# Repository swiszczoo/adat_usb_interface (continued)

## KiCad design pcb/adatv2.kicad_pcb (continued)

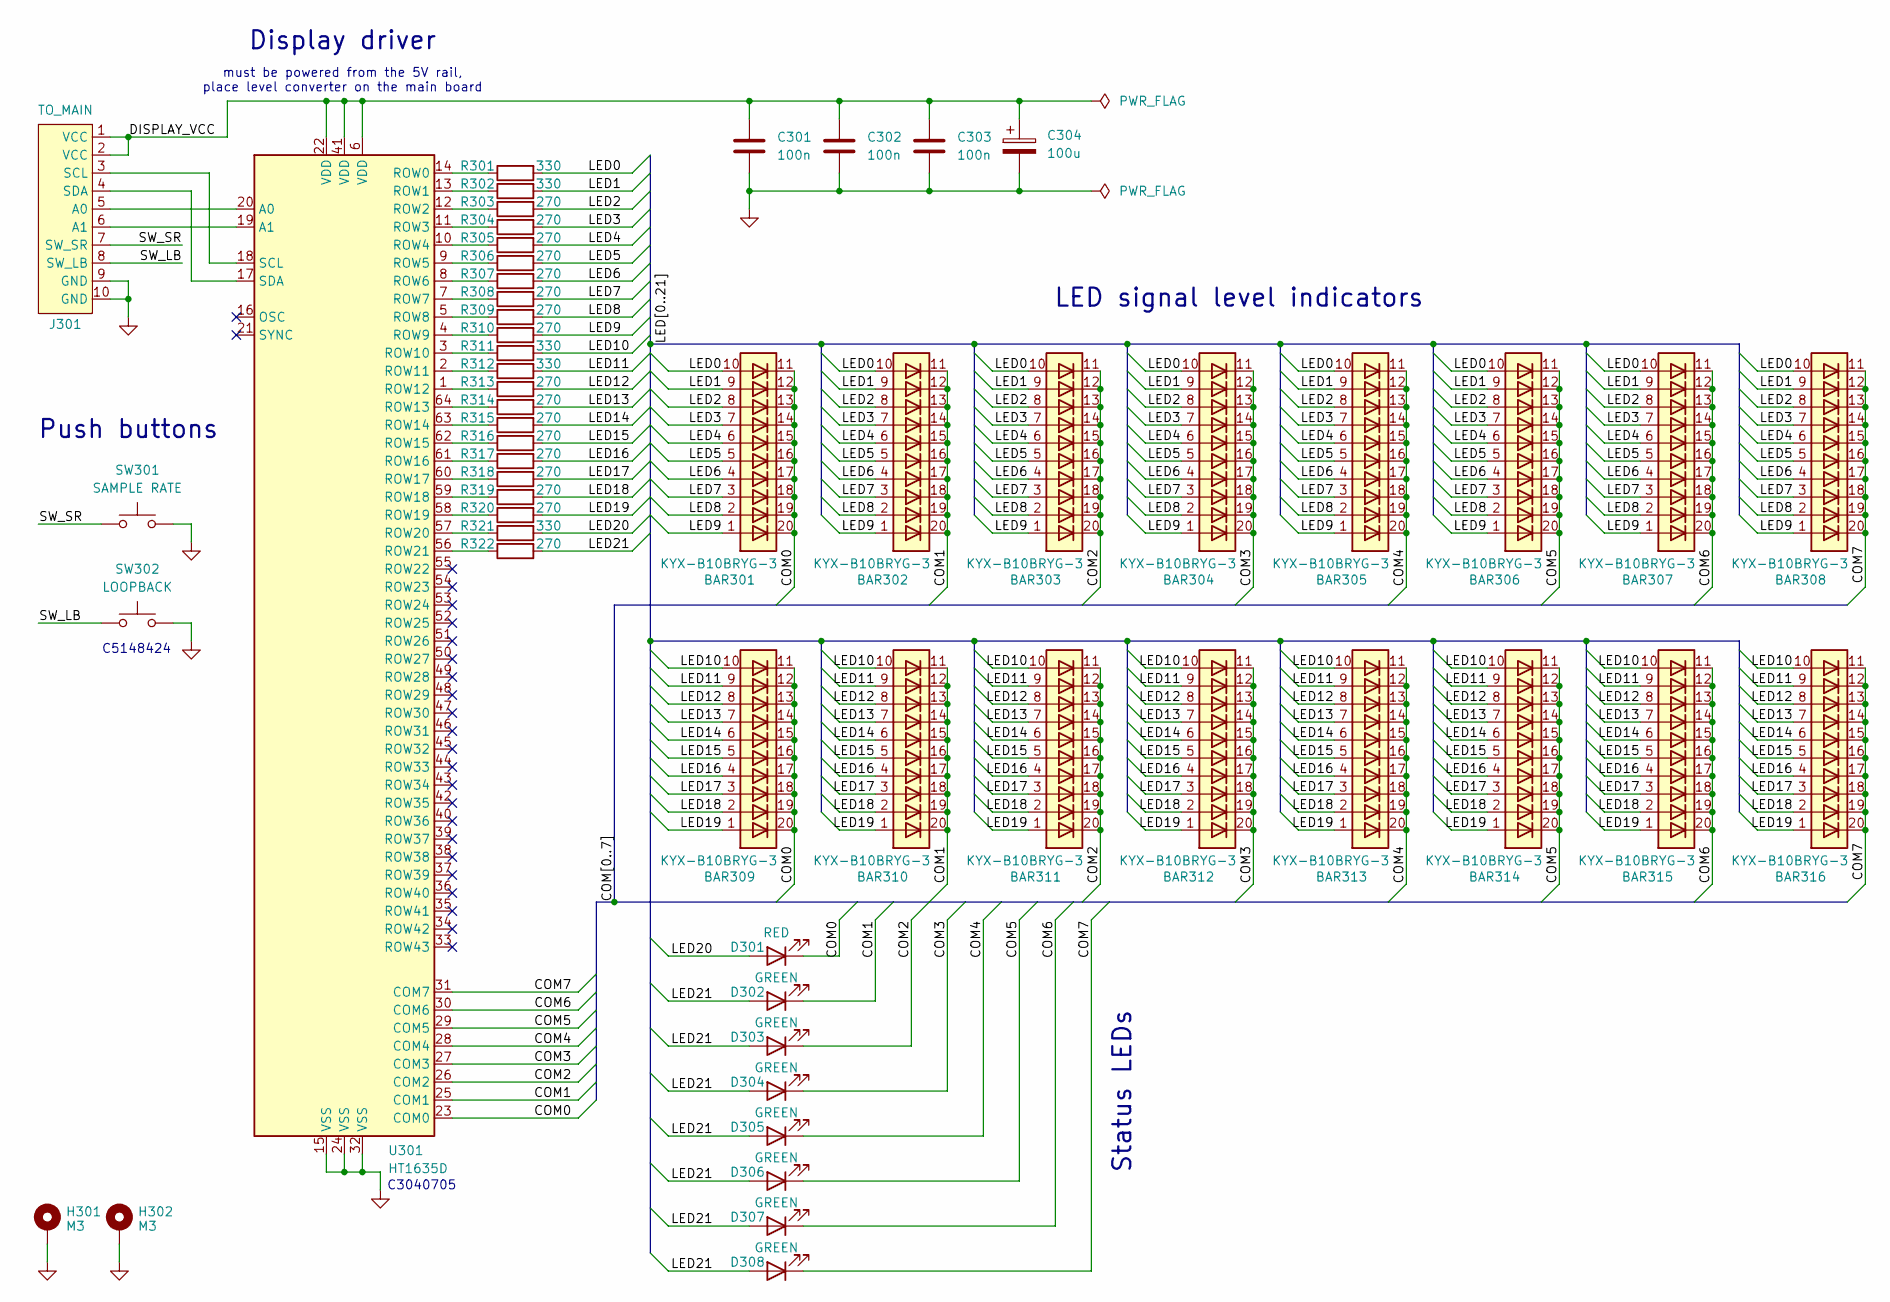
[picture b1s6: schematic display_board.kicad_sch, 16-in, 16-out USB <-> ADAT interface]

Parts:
BAR301, BAR302, BAR303, BAR304, BAR305, BAR306, BAR307, BAR308, BAR309, BAR310, BAR311, BAR312, BAR313, BAR314, BAR315, BAR316: KYX-B10BRYG-3; LED_10bar
C301, C302, C303: 100n; C_0805_2012Metric_Pad1.18x1.45mm_HandSolder
C304: 100u; C_Elec_6.3x5.4
D301: RED; LED_THT_W7.0mm_H2.00mm
D302, D303, D304, D305, D306, D307, D308: GREEN; LED_THT_W7.0mm_H2.00mm
H301, H302: M3; MountingHole_3.2mm_M3_Pad
J301: TO_MAIN; IDC-Header_2x05_P2.54mm_Vertical
R301, R302, R311, R312, R321: 330; R_0805_2012Metric_Pad1.20x1.40mm_HandSolder
R303, R304, R305, R306, R307, R308, R309, R310, R313, R314, R315, R316, R317, R318, R319, R320, R322: 270; R_0805_2012Metric_Pad1.20x1.40mm_HandSolder
SW301: SAMPLE RATE; SW_Push_1P1T_NO_CK_PTS125Sx43SMTR
SW302: LOOPBACK; SW_Push_1P1T_NO_CK_PTS125Sx43SMTR
U301: HT1635D; LQFP-64_7x7mm_P0.4mm

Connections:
/Display board/COM0: BAR301.11 (K), BAR301.12 (K), BAR301.13 (K), BAR301.14 (K), BAR301.15 (K), BAR301.16 (K), BAR301.17 (K), BAR301.18 (K), BAR301.19 (K), BAR301.20 (K), BAR309.11 (K), BAR309.12 (K), BAR309.13 (K), BAR309.14 (K), BAR309.15 (K), BAR309.16 (K), BAR309.17 (K), BAR309.18 (K), BAR309.19 (K), BAR309.20 (K), D301.1 (K), U301.23 (COM0)
/Display board/COM1: BAR302.11 (K), BAR302.12 (K), BAR302.13 (K), BAR302.14 (K), BAR302.15 (K), BAR302.16 (K), BAR302.17 (K), BAR302.18 (K), BAR302.19 (K), BAR302.20 (K), BAR310.11 (K), BAR310.12 (K), BAR310.13 (K), BAR310.14 (K), BAR310.15 (K), BAR310.16 (K), BAR310.17 (K), BAR310.18 (K), BAR310.19 (K), BAR310.20 (K), D302.1 (K), U301.25 (COM1)
/Display board/COM2: BAR303.11 (K), BAR303.12 (K), BAR303.13 (K), BAR303.14 (K), BAR303.15 (K), BAR303.16 (K), BAR303.17 (K), BAR303.18 (K), BAR303.19 (K), BAR303.20 (K), BAR311.11 (K), BAR311.12 (K), BAR311.13 (K), BAR311.14 (K), BAR311.15 (K), BAR311.16 (K), BAR311.17 (K), BAR311.18 (K), BAR311.19 (K), BAR311.20 (K), D303.1 (K), U301.26 (COM2)
/Display board/COM3: BAR304.11 (K), BAR304.12 (K), BAR304.13 (K), BAR304.14 (K), BAR304.15 (K), BAR304.16 (K), BAR304.17 (K), BAR304.18 (K), BAR304.19 (K), BAR304.20 (K), BAR312.11 (K), BAR312.12 (K), BAR312.13 (K), BAR312.14 (K), BAR312.15 (K), BAR312.16 (K), BAR312.17 (K), BAR312.18 (K), BAR312.19 (K), BAR312.20 (K), D304.1 (K), U301.27 (COM3)
/Display board/COM4: BAR305.11 (K), BAR305.12 (K), BAR305.13 (K), BAR305.14 (K), BAR305.15 (K), BAR305.16 (K), BAR305.17 (K), BAR305.18 (K), BAR305.19 (K), BAR305.20 (K), BAR313.11 (K), BAR313.12 (K), BAR313.13 (K), BAR313.14 (K), BAR313.15 (K), BAR313.16 (K), BAR313.17 (K), BAR313.18 (K), BAR313.19 (K), BAR313.20 (K), D305.1 (K), U301.28 (COM4)
/Display board/COM5: BAR306.11 (K), BAR306.12 (K), BAR306.13 (K), BAR306.14 (K), BAR306.15 (K), BAR306.16 (K), BAR306.17 (K), BAR306.18 (K), BAR306.19 (K), BAR306.20 (K), BAR314.11 (K), BAR314.12 (K), BAR314.13 (K), BAR314.14 (K), BAR314.15 (K), BAR314.16 (K), BAR314.17 (K), BAR314.18 (K), BAR314.19 (K), BAR314.20 (K), D306.1 (K), U301.29 (COM5)
/Display board/COM6: BAR307.11 (K), BAR307.12 (K), BAR307.13 (K), BAR307.14 (K), BAR307.15 (K), BAR307.16 (K), BAR307.17 (K), BAR307.18 (K), BAR307.19 (K), BAR307.20 (K), BAR315.11 (K), BAR315.12 (K), BAR315.13 (K), BAR315.14 (K), BAR315.15 (K), BAR315.16 (K), BAR315.17 (K), BAR315.18 (K), BAR315.19 (K), BAR315.20 (K), D307.1 (K), U301.30 (COM6)
/Display board/COM7: BAR308.11 (K), BAR308.12 (K), BAR308.13 (K), BAR308.14 (K), BAR308.15 (K), BAR308.16 (K), BAR308.17 (K), BAR308.18 (K), BAR308.19 (K), BAR308.20 (K), BAR316.11 (K), BAR316.12 (K), BAR316.13 (K), BAR316.14 (K), BAR316.15 (K), BAR316.16 (K), BAR316.17 (K), BAR316.18 (K), BAR316.19 (K), BAR316.20 (K), D308.1 (K), U301.31 (COM7)
/Display board/DISPLAY_VCC: C301.1, C302.1, C303.1, C304.1, J301.1 (VCC), J301.2 (VCC), U301.6 (VDD), U301.22 (VDD), U301.41 (VDD)
/Display board/LED0: BAR301.10 (A), BAR302.10 (A), BAR303.10 (A), BAR304.10 (A), BAR305.10 (A), BAR306.10 (A), BAR307.10 (A), BAR308.10 (A), R301.2
/Display board/LED1: BAR301.9 (A), BAR302.9 (A), BAR303.9 (A), BAR304.9 (A), BAR305.9 (A), BAR306.9 (A), BAR307.9 (A), BAR308.9 (A), R302.2
/Display board/LED2: BAR301.8 (A), BAR302.8 (A), BAR303.8 (A), BAR304.8 (A), BAR305.8 (A), BAR306.8 (A), BAR307.8 (A), BAR308.8 (A), R303.2
/Display board/LED3: BAR301.7 (A), BAR302.7 (A), BAR303.7 (A), BAR304.7 (A), BAR305.7 (A), BAR306.7 (A), BAR307.7 (A), BAR308.7 (A), R304.2
/Display board/LED4: BAR301.6 (A), BAR302.6 (A), BAR303.6 (A), BAR304.6 (A), BAR305.6 (A), BAR306.6 (A), BAR307.6 (A), BAR308.6 (A), R305.2
/Display board/LED5: BAR301.5 (A), BAR302.5 (A), BAR303.5 (A), BAR304.5 (A), BAR305.5 (A), BAR306.5 (A), BAR307.5 (A), BAR308.5 (A), R306.2
/Display board/LED6: BAR301.4 (A), BAR302.4 (A), BAR303.4 (A), BAR304.4 (A), BAR305.4 (A), BAR306.4 (A), BAR307.4 (A), BAR308.4 (A), R307.2
/Display board/LED7: BAR301.3 (A), BAR302.3 (A), BAR303.3 (A), BAR304.3 (A), BAR305.3 (A), BAR306.3 (A), BAR307.3 (A), BAR308.3 (A), R308.2
/Display board/LED8: BAR301.2 (A), BAR302.2 (A), BAR303.2 (A), BAR304.2 (A), BAR305.2 (A), BAR306.2 (A), BAR307.2 (A), BAR308.2 (A), R309.2
/Display board/LED9: BAR301.1 (A), BAR302.1 (A), BAR303.1 (A), BAR304.1 (A), BAR305.1 (A), BAR306.1 (A), BAR307.1 (A), BAR308.1 (A), R310.2
/Display board/LED10: BAR309.10 (A), BAR310.10 (A), BAR311.10 (A), BAR312.10 (A), BAR313.10 (A), BAR314.10 (A), BAR315.10 (A), BAR316.10 (A), R311.2
/Display board/LED11: BAR309.9 (A), BAR310.9 (A), BAR311.9 (A), BAR312.9 (A), BAR313.9 (A), BAR314.9 (A), BAR315.9 (A), BAR316.9 (A), R312.2
/Display board/LED12: BAR309.8 (A), BAR310.8 (A), BAR311.8 (A), BAR312.8 (A), BAR313.8 (A), BAR314.8 (A), BAR315.8 (A), BAR316.8 (A), R313.2
/Display board/LED13: BAR309.7 (A), BAR310.7 (A), BAR311.7 (A), BAR312.7 (A), BAR313.7 (A), BAR314.7 (A), BAR315.7 (A), BAR316.7 (A), R314.2
/Display board/LED14: BAR309.6 (A), BAR310.6 (A), BAR311.6 (A), BAR312.6 (A), BAR313.6 (A), BAR314.6 (A), BAR315.6 (A), BAR316.6 (A), R315.2
/Display board/LED15: BAR309.5 (A), BAR310.5 (A), BAR311.5 (A), BAR312.5 (A), BAR313.5 (A), BAR314.5 (A), BAR315.5 (A), BAR316.5 (A), R316.2
/Display board/LED16: BAR309.4 (A), BAR310.4 (A), BAR311.4 (A), BAR312.4 (A), BAR313.4 (A), BAR314.4 (A), BAR315.4 (A), BAR316.4 (A), R317.2
/Display board/LED17: BAR309.3 (A), BAR310.3 (A), BAR311.3 (A), BAR312.3 (A), BAR313.3 (A), BAR314.3 (A), BAR315.3 (A), BAR316.3 (A), R318.2
/Display board/LED18: BAR309.2 (A), BAR310.2 (A), BAR311.2 (A), BAR312.2 (A), BAR313.2 (A), BAR314.2 (A), BAR315.2 (A), BAR316.2 (A), R319.2
/Display board/LED19: BAR309.1 (A), BAR310.1 (A), BAR311.1 (A), BAR312.1 (A), BAR313.1 (A), BAR314.1 (A), BAR315.1 (A), BAR316.1 (A), R320.2
/Display board/LED20: D301.2 (A), R321.2
/Display board/LED21: D302.2 (A), D303.2 (A), D304.2 (A), D305.2 (A), D306.2 (A), D307.2 (A), D308.2 (A), R322.2
/Display board/SW_LB: J301.8 (SW_LB), SW302.1
/Display board/SW_SR: J301.7 (SW_SR), SW301.1
DISPLAY_GND: C301.2, C302.2, C303.2, C304.2, H301.1, H302.1, J301.9 (GND), J301.10 (GND), SW301.2, SW302.2, U301.15 (VSS), U301.24 (VSS), U301.32 (VSS)
unnamed: J301.5 (A0), U301.20 (A0)
unnamed: J301.6 (A1), U301.19 (A1)
unnamed: J301.3 (SCL), U301.18 (SCL)
unnamed: J301.4 (SDA), U301.17 (SDA)
unnamed: R301.1, U301.14 (ROW0)
unnamed: R302.1, U301.13 (ROW1)
unnamed: R303.1, U301.12 (ROW2)
unnamed: R304.1, U301.11 (ROW3)
unnamed: R305.1, U301.10 (ROW4)
unnamed: R306.1, U301.9 (ROW5)
unnamed: R307.1, U301.8 (ROW6)
unnamed: R308.1, U301.7 (ROW7)
unnamed: R309.1, U301.5 (ROW8)
unnamed: R310.1, U301.4 (ROW9)
unnamed: R311.1, U301.3 (ROW10)
unnamed: R312.1, U301.2 (ROW11)
unnamed: R313.1, U301.1 (ROW12)
unnamed: R314.1, U301.64 (ROW13)
unnamed: R315.1, U301.63 (ROW14)
unnamed: R316.1, U301.62 (ROW15)
unnamed: R317.1, U301.61 (ROW16)
unnamed: R318.1, U301.60 (ROW17)
unnamed: R319.1, U301.59 (ROW18)
unnamed: R320.1, U301.58 (ROW19)
unnamed: R321.1, U301.57 (ROW20)
unnamed: R322.1, U301.56 (ROW21)

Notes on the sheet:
C3040705
Status LEDs
Display driver
LED signal level indicators
C5148424
must be powered from the 5V rail, place level converter on the main board
Push buttons

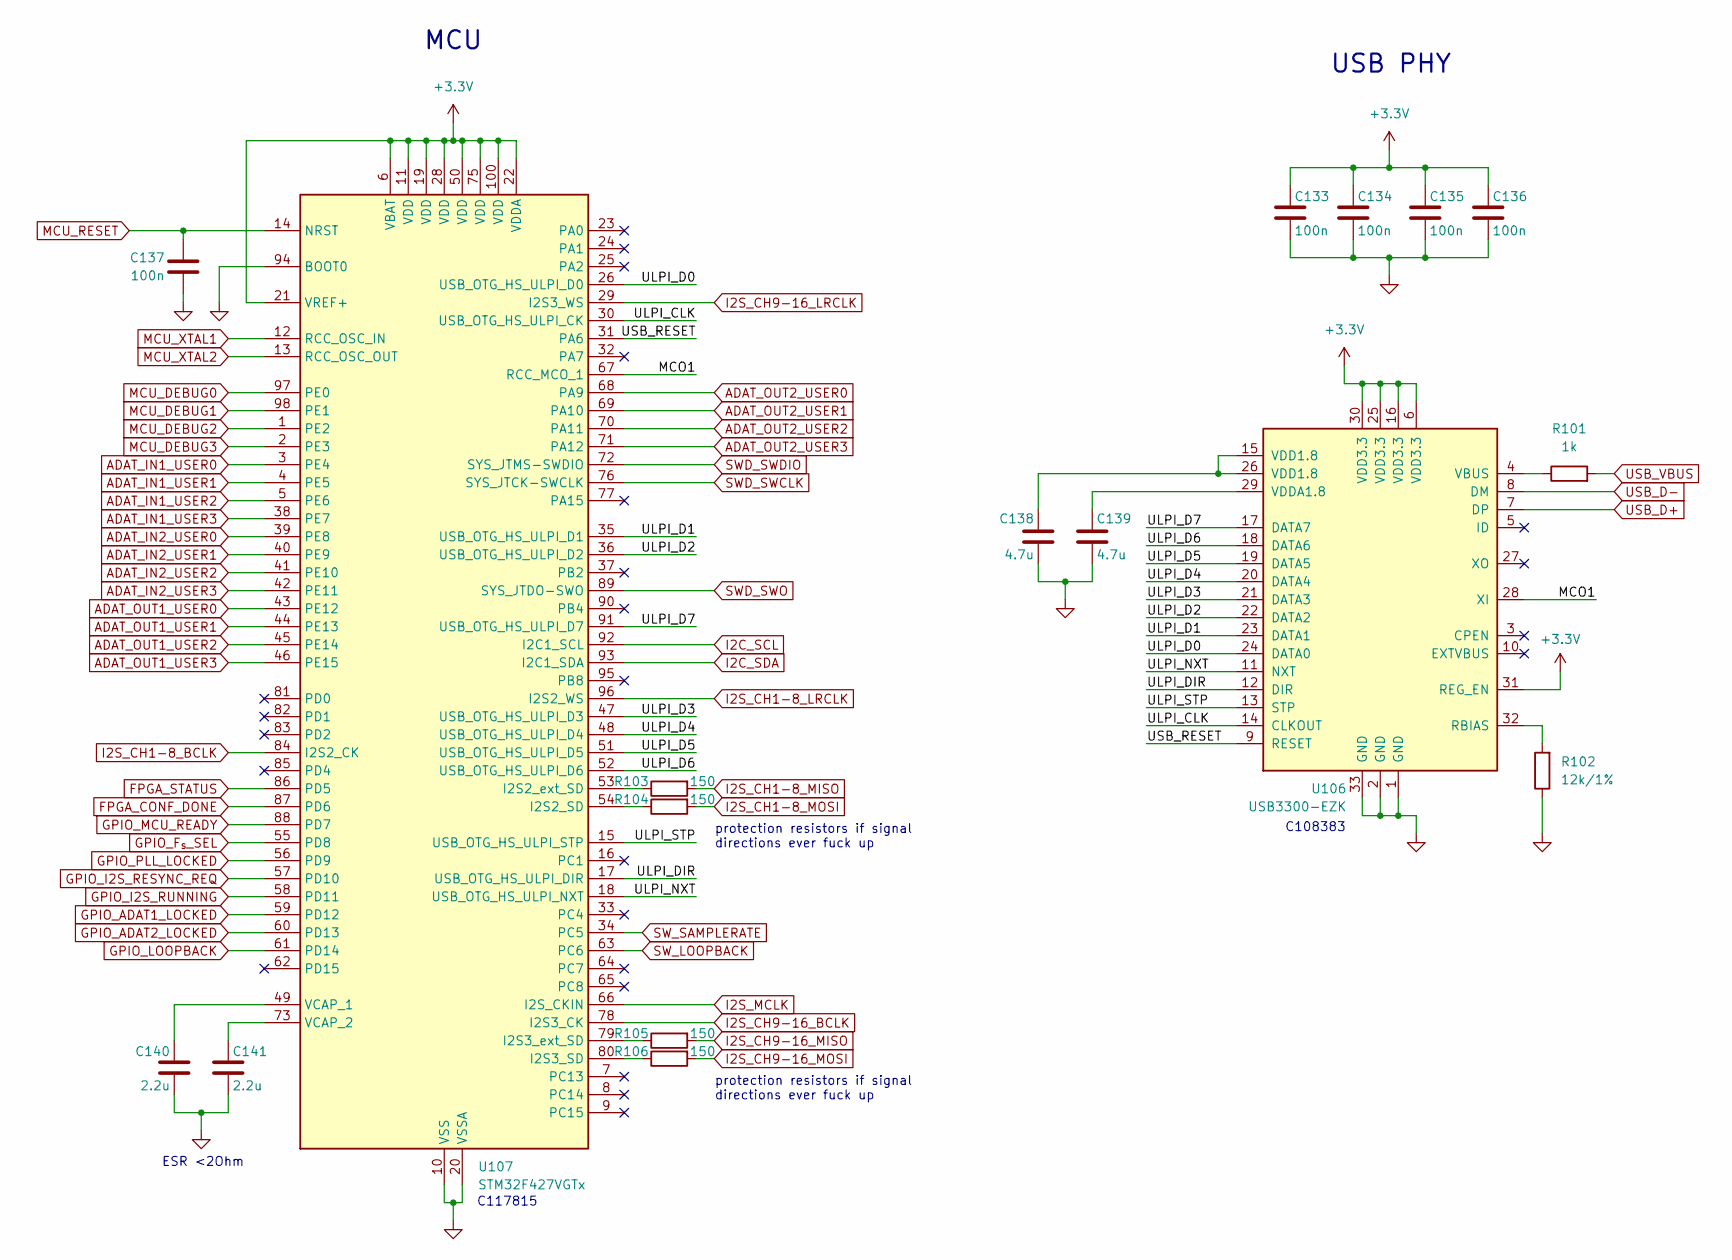
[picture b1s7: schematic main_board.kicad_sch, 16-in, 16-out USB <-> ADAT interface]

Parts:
C133, C134, C135, C136, C137: 100n; C_0805_2012Metric_Pad1.18x1.45mm_HandSolder
C138, C139: 4.7u; C_0805_2012Metric_Pad1.18x1.45mm_HandSolder
C140, C141: 2.2u; C_0805_2012Metric_Pad1.18x1.45mm_HandSolder
R101: 1k; R_0805_2012Metric_Pad1.20x1.40mm_HandSolder
R102: 12k/1%; R_0805_2012Metric_Pad1.20x1.40mm_HandSolder
R103, R104, R105, R106: 150; R_0805_2012Metric_Pad1.20x1.40mm_HandSolder
U106: USB3300-EZK; QFN-32-1EP_5x5mm_P0.5mm_EP3.45x3.45mm
U107: STM32F427VGTx; LQFP-100_14x14mm_P0.5mm

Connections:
+3.3V: C133.1, C134.1, C135.1, C136.1, U106.6 (VDD3.3), U106.16 (VDD3.3), U106.25 (VDD3.3), U106.30 (VDD3.3), U106.31 (REG_EN), U107.6 (VBAT), U107.11 (VDD), U107.19 (VDD), U107.21 (VREF+), U107.22 (VDDA), U107.28 (VDD), U107.50 (VDD), U107.75 (VDD), U107.100 (VDD); also elsewhere on the board
/MCU and USB/MCO1: U106.28 (XI), U107.67 (RCC_MCO_1)
/MCU and USB/ULPI_CLK: U106.14 (CLKOUT), U107.30 (USB_OTG_HS_ULPI_CK)
/MCU and USB/ULPI_D0: U106.24 (DATA0), U107.26 (USB_OTG_HS_ULPI_D0)
/MCU and USB/ULPI_D1: U106.23 (DATA1), U107.35 (USB_OTG_HS_ULPI_D1)
/MCU and USB/ULPI_D2: U106.22 (DATA2), U107.36 (USB_OTG_HS_ULPI_D2)
/MCU and USB/ULPI_D3: U106.21 (DATA3), U107.47 (USB_OTG_HS_ULPI_D3)
/MCU and USB/ULPI_D4: U106.20 (DATA4), U107.48 (USB_OTG_HS_ULPI_D4)
/MCU and USB/ULPI_D5: U106.19 (DATA5), U107.51 (USB_OTG_HS_ULPI_D5)
/MCU and USB/ULPI_D6: U106.18 (DATA6), U107.52 (USB_OTG_HS_ULPI_D6)
/MCU and USB/ULPI_D7: U106.17 (DATA7), U107.91 (USB_OTG_HS_ULPI_D7)
/MCU and USB/ULPI_DIR: U106.12 (DIR), U107.17 (USB_OTG_HS_ULPI_DIR)
/MCU and USB/ULPI_NXT: U106.11 (NXT), U107.18 (USB_OTG_HS_ULPI_NXT)
/MCU and USB/ULPI_STP: U106.13 (STP), U107.15 (USB_OTG_HS_ULPI_STP)
/MCU and USB/USB_RESET: U106.9 (RESET), U107.31 (PA6)
ADAT_IN1_USER0: U107.3 (PE4); also elsewhere on the board
ADAT_IN1_USER1: U107.4 (PE5); also elsewhere on the board
ADAT_IN1_USER2: U107.5 (PE6); also elsewhere on the board
ADAT_IN1_USER3: U107.38 (PE7); also elsewhere on the board
ADAT_IN2_USER0: U107.39 (PE8); also elsewhere on the board
ADAT_IN2_USER1: U107.40 (PE9); also elsewhere on the board
ADAT_IN2_USER2: U107.41 (PE10); also elsewhere on the board
ADAT_IN2_USER3: U107.42 (PE11); also elsewhere on the board
ADAT_OUT1_USER0: U107.43 (PE12); also elsewhere on the board
ADAT_OUT1_USER1: U107.44 (PE13); also elsewhere on the board
ADAT_OUT1_USER2: U107.45 (PE14); also elsewhere on the board
ADAT_OUT1_USER3: U107.46 (PE15); also elsewhere on the board
ADAT_OUT2_USER0: U107.68 (PA9); also elsewhere on the board
ADAT_OUT2_USER1: U107.69 (PA10); also elsewhere on the board
ADAT_OUT2_USER2: U107.70 (PA11); also elsewhere on the board
ADAT_OUT2_USER3: U107.71 (PA12); also elsewhere on the board
FPGA_CONF_DONE: U107.87 (PD6); also elsewhere on the board
FPGA_STATUS: U107.86 (PD5); also elsewhere on the board
GND: C133.2, C134.2, C135.2, C136.2, C137.2, C138.2, C139.2, C140.2, C141.2, R102.1, U106.1 (GND), U106.2 (GND), U106.33 (GND), U107.10 (VSS), U107.20 (VSSA), U107.27 (VSS), U107.74 (VSS), U107.94 (BOOT0), U107.99 (VSS); also elsewhere on the board
GPIO_ADAT1_LOCKED: U107.59 (PD12); also elsewhere on the board
GPIO_ADAT2_LOCKED: U107.60 (PD13); also elsewhere on the board
GPIO_F_{s}_SEL: U107.55 (PD8); also elsewhere on the board
GPIO_I2S_RESYNC_REQ: U107.57 (PD10); also elsewhere on the board
GPIO_I2S_RUNNING: U107.58 (PD11); also elsewhere on the board
GPIO_LOOPBACK: U107.61 (PD14); also elsewhere on the board
GPIO_MCU_READY: U107.88 (PD7); also elsewhere on the board
GPIO_PLL_LOCKED: U107.56 (PD9); also elsewhere on the board
I2C_SCL: U107.92 (I2C1_SCL); also elsewhere on the board
I2C_SDA: U107.93 (I2C1_SDA); also elsewhere on the board
I2S_CH1-8_BCLK: U107.84 (I2S2_CK); also elsewhere on the board
I2S_CH1-8_LRCLK: U107.96 (I2S2_WS); also elsewhere on the board
I2S_CH1-8_MISO: R103.2; also elsewhere on the board
I2S_CH1-8_MOSI: R104.2; also elsewhere on the board
I2S_CH9-16_BCLK: U107.78 (I2S3_CK); also elsewhere on the board
I2S_CH9-16_LRCLK: U107.29 (I2S3_WS); also elsewhere on the board
I2S_CH9-16_MISO: R105.2; also elsewhere on the board
I2S_CH9-16_MOSI: R106.2; also elsewhere on the board
I2S_MCLK: U107.66 (I2S_CKIN); also elsewhere on the board
MCU_DEBUG0: U107.97 (PE0); also elsewhere on the board
MCU_DEBUG1: U107.98 (PE1); also elsewhere on the board
MCU_DEBUG2: U107.1 (PE2); also elsewhere on the board
MCU_DEBUG3: U107.2 (PE3); also elsewhere on the board
MCU_RESET: C137.1, U107.14 (NRST); also elsewhere on the board
MCU_XTAL1: U107.12 (RCC_OSC_IN); also elsewhere on the board
MCU_XTAL2: U107.13 (RCC_OSC_OUT); also elsewhere on the board
unnamed: C138.1, U106.15 (VDD1.8), U106.26 (VDD1.8)
unnamed: R102.2, U106.32 (RBIAS)
unnamed: R101.1, U106.4 (VBUS)
unnamed: C139.1, U106.29 (VDDA1.8)
unnamed: R103.1, U107.53 (I2S2_ext_SD)
unnamed: R104.1, U107.54 (I2S2_SD)
unnamed: R105.1, U107.79 (I2S3_ext_SD)
unnamed: R106.1, U107.80 (I2S3_SD)
unnamed: C140.1, U107.49 (VCAP_1)
unnamed: C141.1, U107.73 (VCAP_2)
SWD_SWCLK: U107.76 (SYS_JTCK-SWCLK); also elsewhere on the board
SWD_SWDIO: U107.72 (SYS_JTMS-SWDIO); also elsewhere on the board
SWD_SWO: U107.89 (SYS_JTDO-SWO); also elsewhere on the board
SW_LOOPBACK: U107.63 (PC6); also elsewhere on the board
SW_SAMPLERATE: U107.34 (PC5); also elsewhere on the board
USB_D+: U106.7 (DP); also elsewhere on the board
USB_D-: U106.8 (DM); also elsewhere on the board
USB_VBUS: R101.2; also elsewhere on the board

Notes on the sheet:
USB PHY
C108383
MCU
protection resistors if signal directions ever fuck up
C117815
ESR <2Ohm

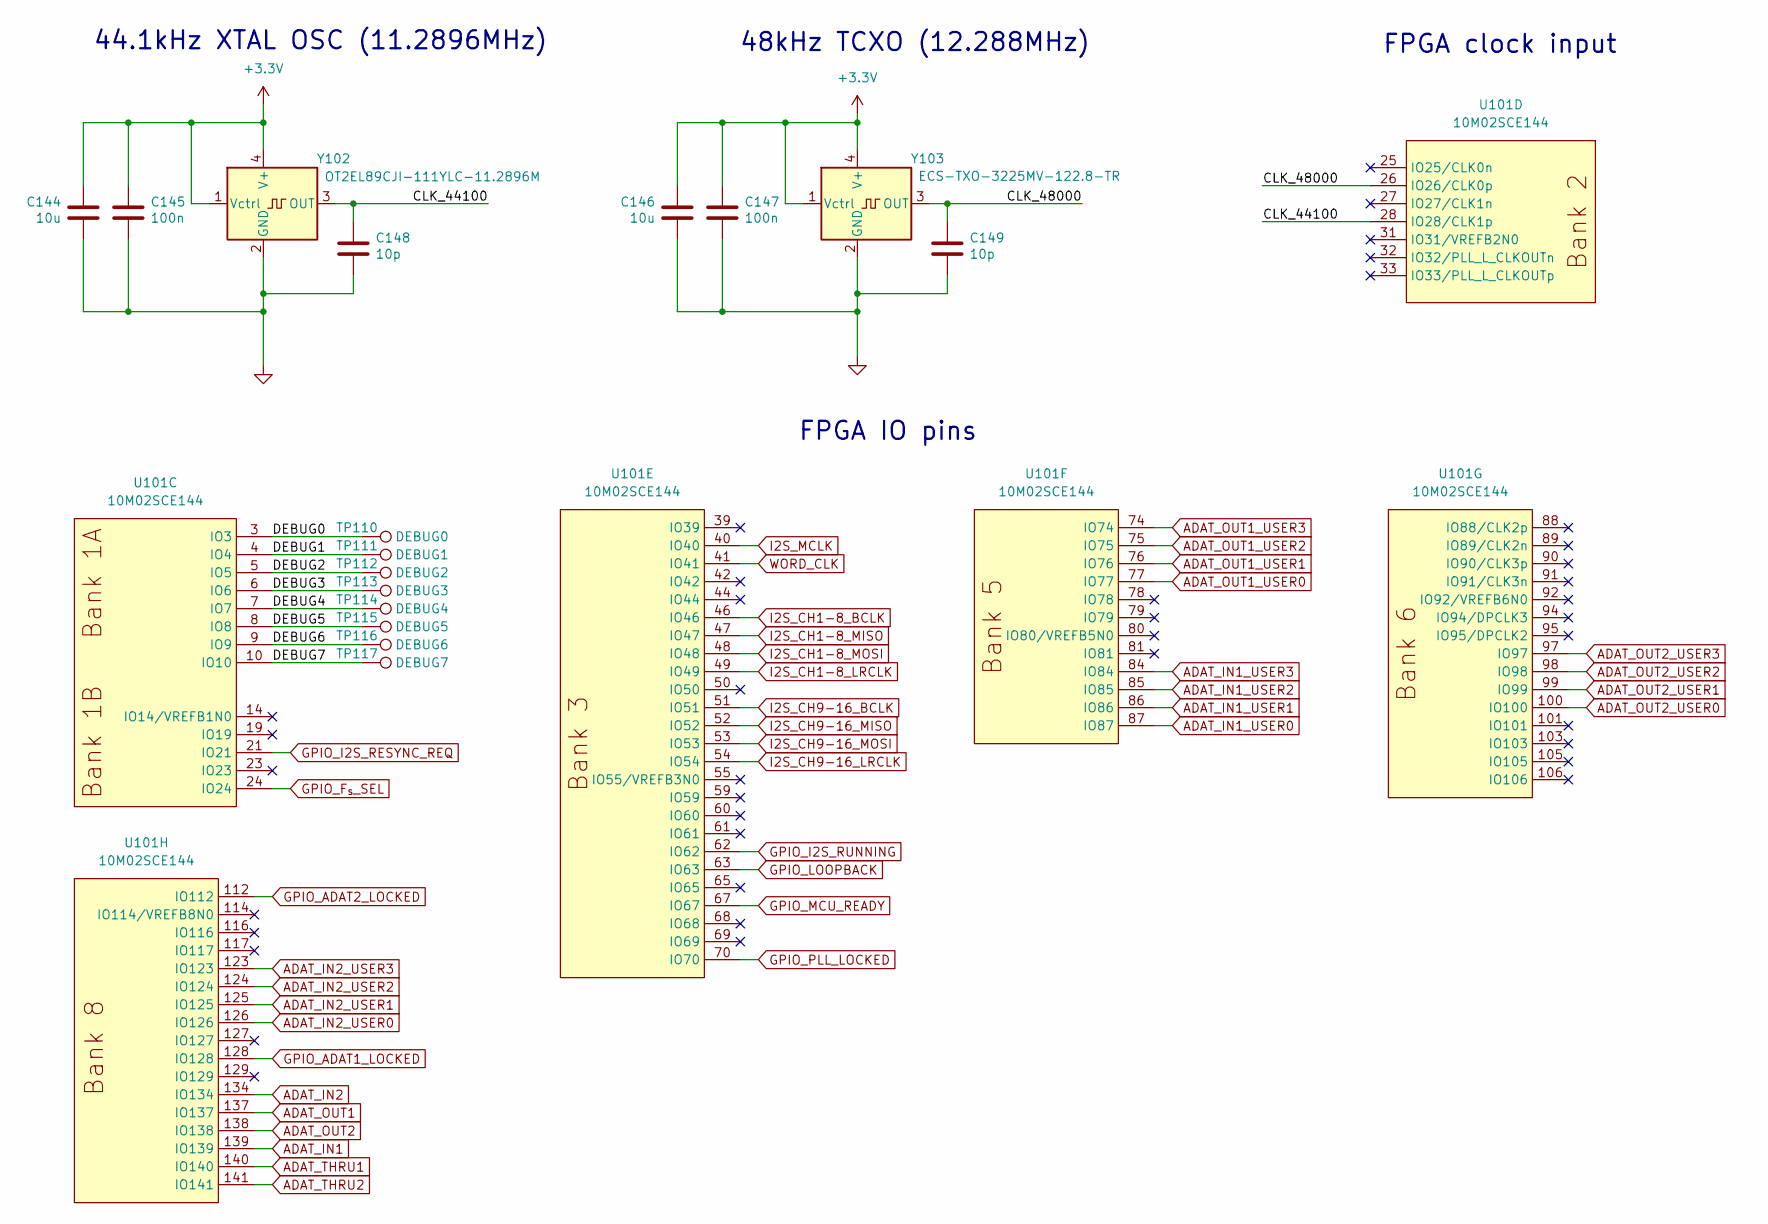
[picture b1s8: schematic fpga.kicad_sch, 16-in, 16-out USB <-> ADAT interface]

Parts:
C144, C146: 10u; C_1206_3216Metric_Pad1.33x1.80mm_HandSolder
C145, C147: 100n; C_0805_2012Metric_Pad1.18x1.45mm_HandSolder
C148, C149: 10p; C_0805_2012Metric_Pad1.18x1.45mm_HandSolder
TP110: DEBUG0; TestPoint_Pad_D2.5mm
TP111: DEBUG1; TestPoint_Pad_D2.5mm
TP112: DEBUG2; TestPoint_Pad_D2.5mm
TP113: DEBUG3; TestPoint_Pad_D2.5mm
TP114: DEBUG4; TestPoint_Pad_D2.5mm
TP115: DEBUG5; TestPoint_Pad_D2.5mm
TP116: DEBUG6; TestPoint_Pad_D2.5mm
TP117: DEBUG7; TestPoint_Pad_D2.5mm
U101: 10M02SCE144; EQFP-144-1EP_20x20mm_P0.5mm_EP4x4mm
Y102: OT2EL89CJI-111YLC-11.2896M; Oscillator_SMD_Abracon_ASE-4Pin_3.2x2.5mm_HandSoldering
Y103: ECS-TXO-3225MV-122.8-TR; Oscillator_SMD_Abracon_ASE-4Pin_3.2x2.5mm_HandSoldering

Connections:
+3.3V: C144.1, C145.1, C146.1, C147.1, Y102.1 (Vctrl), Y102.4 (V+), Y103.1 (Vctrl), Y103.4 (V+); also elsewhere on the board
/FPGA and clock generators/CLK_44100: C148.1, U101.28 (IO28/CLK1p), Y102.3 (OUT)
/FPGA and clock generators/CLK_48000: C149.1, U101.26 (IO26/CLK0p), Y103.3 (OUT)
/FPGA and clock generators/DEBUG0: TP110.1, U101.3 (IO3)
/FPGA and clock generators/DEBUG1: TP111.1, U101.4 (IO4)
/FPGA and clock generators/DEBUG2: TP112.1, U101.5 (IO5)
/FPGA and clock generators/DEBUG3: TP113.1, U101.6 (IO6)
/FPGA and clock generators/DEBUG4: TP114.1, U101.7 (IO7)
/FPGA and clock generators/DEBUG5: TP115.1, U101.8 (IO8)
/FPGA and clock generators/DEBUG6: TP116.1, U101.9 (IO9)
/FPGA and clock generators/DEBUG7: TP117.1, U101.10 (IO10)
ADAT_IN1: U101.139 (IO139); also elsewhere on the board
ADAT_IN1_USER0: U101.87 (IO87); also elsewhere on the board
ADAT_IN1_USER1: U101.86 (IO86); also elsewhere on the board
ADAT_IN1_USER2: U101.85 (IO85); also elsewhere on the board
ADAT_IN1_USER3: U101.84 (IO84); also elsewhere on the board
ADAT_IN2: U101.134 (IO134); also elsewhere on the board
ADAT_IN2_USER0: U101.126 (IO126); also elsewhere on the board
ADAT_IN2_USER1: U101.125 (IO125); also elsewhere on the board
ADAT_IN2_USER2: U101.124 (IO124); also elsewhere on the board
ADAT_IN2_USER3: U101.123 (IO123); also elsewhere on the board
ADAT_OUT1: U101.137 (IO137); also elsewhere on the board
ADAT_OUT1_USER0: U101.77 (IO77); also elsewhere on the board
ADAT_OUT1_USER1: U101.76 (IO76); also elsewhere on the board
ADAT_OUT1_USER2: U101.75 (IO75); also elsewhere on the board
ADAT_OUT1_USER3: U101.74 (IO74); also elsewhere on the board
ADAT_OUT2: U101.138 (IO138); also elsewhere on the board
ADAT_OUT2_USER0: U101.100 (IO100); also elsewhere on the board
ADAT_OUT2_USER1: U101.99 (IO99); also elsewhere on the board
ADAT_OUT2_USER2: U101.98 (IO98); also elsewhere on the board
ADAT_OUT2_USER3: U101.97 (IO97); also elsewhere on the board
ADAT_THRU1: U101.140 (IO140); also elsewhere on the board
ADAT_THRU2: U101.141 (IO141); also elsewhere on the board
GND: C144.2, C145.2, C146.2, C147.2, C148.2, C149.2, Y102.2 (GND), Y103.2 (GND); also elsewhere on the board
GPIO_ADAT1_LOCKED: U101.128 (IO128); also elsewhere on the board
GPIO_ADAT2_LOCKED: U101.112 (IO112); also elsewhere on the board
GPIO_F_{s}_SEL: U101.24 (IO24); also elsewhere on the board
GPIO_I2S_RESYNC_REQ: U101.21 (IO21); also elsewhere on the board
GPIO_I2S_RUNNING: U101.62 (IO62); also elsewhere on the board
GPIO_LOOPBACK: U101.63 (IO63); also elsewhere on the board
GPIO_MCU_READY: U101.67 (IO67); also elsewhere on the board
GPIO_PLL_LOCKED: U101.70 (IO70); also elsewhere on the board
I2S_CH1-8_BCLK: U101.46 (IO46); also elsewhere on the board
I2S_CH1-8_LRCLK: U101.49 (IO49); also elsewhere on the board
I2S_CH1-8_MISO: U101.47 (IO47); also elsewhere on the board
I2S_CH1-8_MOSI: U101.48 (IO48); also elsewhere on the board
I2S_CH9-16_BCLK: U101.51 (IO51); also elsewhere on the board
I2S_CH9-16_LRCLK: U101.54 (IO54); also elsewhere on the board
I2S_CH9-16_MISO: U101.52 (IO52); also elsewhere on the board
I2S_CH9-16_MOSI: U101.53 (IO53); also elsewhere on the board
I2S_MCLK: U101.40 (IO40); also elsewhere on the board
WORD_CLK: U101.41 (IO41); also elsewhere on the board

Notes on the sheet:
48kHz TCXO (12.288MHz)
44.1kHz XTAL OSC (11.2896MHz)
FPGA IO pins
FPGA clock input

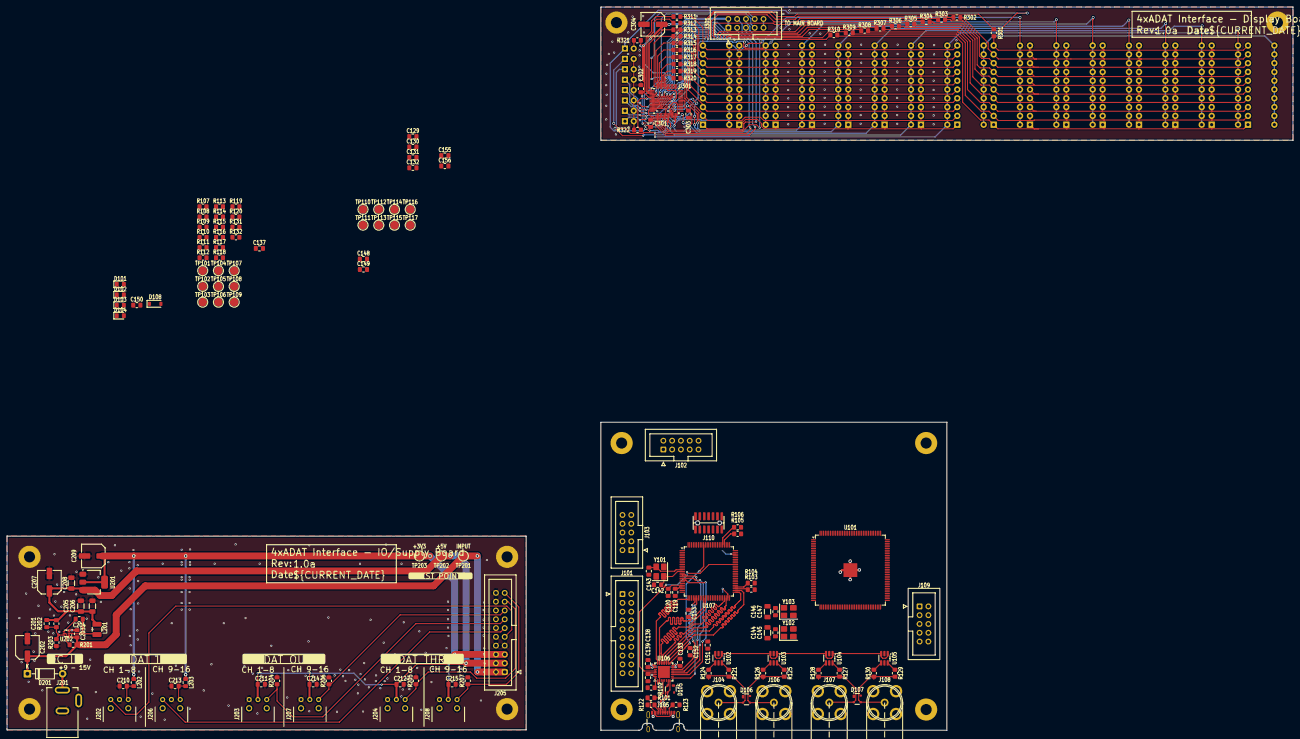
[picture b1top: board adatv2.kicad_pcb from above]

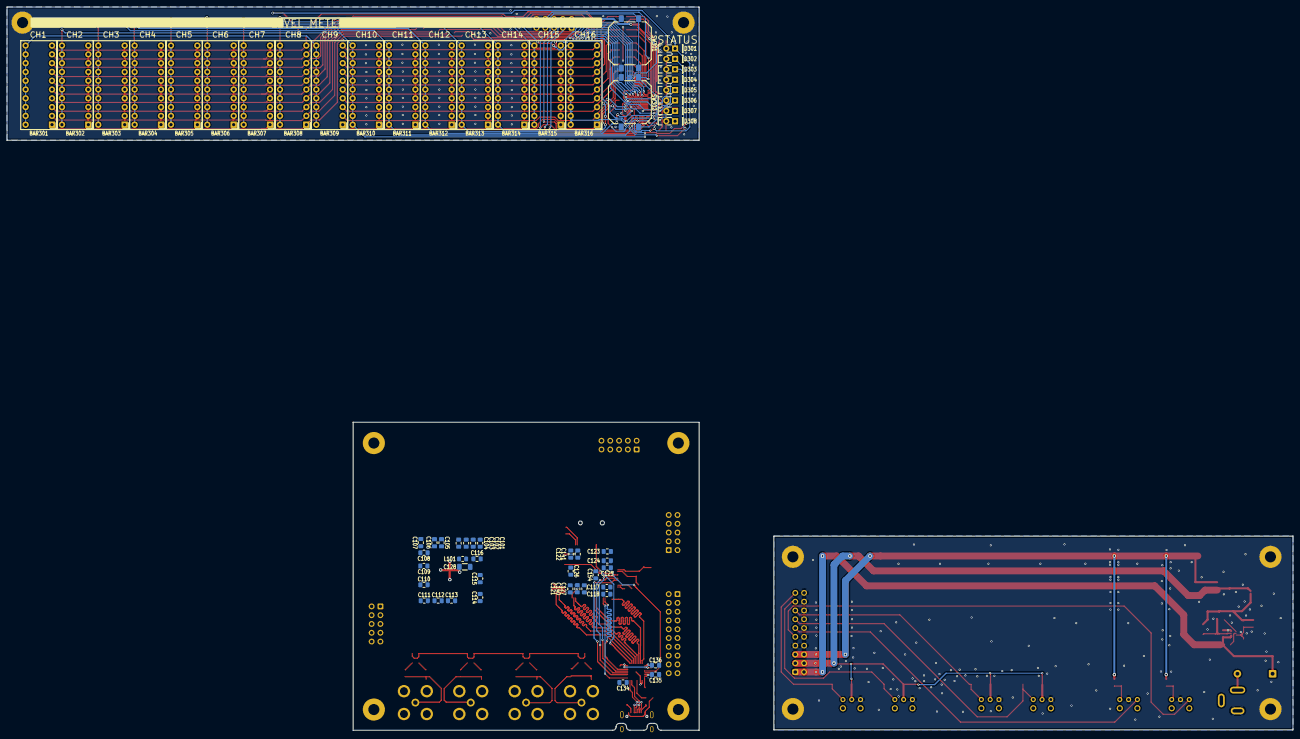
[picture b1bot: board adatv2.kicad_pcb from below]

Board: 4 copper layers, 371.6 x 209.0 mm, 237 parts (59 on the bottom side), 201 nets.

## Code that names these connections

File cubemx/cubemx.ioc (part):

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Mcu.Name=STM32F427V(G-I)Tx
Mcu.Package=LQFP100
Mcu.UserName=STM32F427VGTx
PA10.GPIOParameters=GPIO_Label
PA10.GPIO_Label=ADAT_OUT2_USER1
PA10.Signal=GPIO_Output
PA11.GPIOParameters=GPIO_Label
PA11.GPIO_Label=ADAT_OUT2_USER2
PA11.Signal=GPIO_Output
PA12.GPIOParameters=GPIO_Label
PA12.GPIO_Label=ADAT_OUT2_USER3
PA12.Signal=GPIO_Output
PA13.Mode=Trace_Asynchronous_SW
PA13.Signal=SYS_JTMS-SWDIO
PA14.Mode=Trace_Asynchronous_SW
PA14.Signal=SYS_JTCK-SWCLK
PA3.Mode=Device_HS
PA3.Signal=USB_OTG_HS_ULPI_D0
PA4.Mode=Full_Duplex_Slave
PA4.Signal=I2S3_WS
PA5.Mode=Device_HS
PA5.Signal=USB_OTG_HS_ULPI_CK
PA8.Mode=Clock-out-1
PA8.Signal=RCC_MCO_1
PA9.GPIOParameters=GPIO_Label
PA9.GPIO_Label=ADAT_OUT2_USER0
PA9.Signal=GPIO_Output
PB0.Mode=Device_HS
PB0.Signal=USB_OTG_HS_ULPI_D1
PB1.Mode=Device_HS
PB1.Signal=USB_OTG_HS_ULPI_D2
PB10.Mode=Device_HS
PB10.Signal=USB_OTG_HS_ULPI_D3
PB11.Mode=Device_HS
PB11.Signal=USB_OTG_HS_ULPI_D4
PB12.Mode=Device_HS
PB12.Signal=USB_OTG_HS_ULPI_D5
PB13.Mode=Device_HS
PB13.Signal=USB_OTG_HS_ULPI_D6
PB14.Mode=Full_Duplex_Slave
PB14.Signal=I2S2_ext_SD
PB15.Mode=Full_Duplex_Slave
PB15.Signal=I2S2_SD
PB3.Mode=Trace_Asynchronous_SW
PB3.Signal=SYS_JTDO-SWO
PB5.Mode=Device_HS
PB5.Signal=USB_OTG_HS_ULPI_D7
PB6.Mode=I2C
PB6.Signal=I2C1_SCL
PB7.Mode=I2C
PB7.Signal=I2C1_SDA
PB9.Mode=Full_Duplex_Slave
PB9.Signal=I2S2_WS
PC0.Mode=Device_HS
PC0.Signal=USB_OTG_HS_ULPI_STP
PC10.Mode=Full_Duplex_Slave
PC10.Signal=I2S3_CK
PC11.Mode=Full_Duplex_Slave
PC11.Signal=I2S3_ext_SD
PC12.Mode=Full_Duplex_Slave
PC12.Signal=I2S3_SD
PC2.Mode=Device_HS
PC2.Signal=USB_OTG_HS_ULPI_DIR
PC3.Mode=Device_HS
PC3.Signal=USB_OTG_HS_ULPI_NXT
PC5.GPIOParameters=GPIO_Label
PC5.GPIO_Label=SW_SAMPLERATE
PC5.Signal=GPIO_Input
PC6.GPIOParameters=GPIO_Label
PC6.GPIO_Label=SW_LOOPBACK
PC6.Signal=GPIO_Input
PC9.Mode=Audio_ClockIn
PC9.Signal=I2S_CKIN
PD10.GPIOParameters=GPIO_Label
PD10.GPIO_Label=I2S_RESYNC_REQ
PD10.Signal=GPIO_Output
PD11.GPIOParameters=GPIO_Label
PD11.GPIO_Label=I2S_RUNNING
PD11.Signal=GPIO_Input
PD12.GPIOParameters=GPIO_Label
PD12.GPIO_Label=ADAT1_LOCKED
PD12.Signal=GPIO_Input
PD13.GPIOParameters=GPIO_Label
PD13.GPIO_Label=ADAT2_LOCKED
PD13.Signal=GPIO_Input
PD14.GPIOParameters=GPIO_Label
PD14.GPIO_Label=LOOPBACK
PD14.Signal=GPIO_Output
PD3.Mode=Full_Duplex_Slave
PD3.Signal=I2S2_CK
PD5.GPIOParameters=GPIO_Label
PD5.GPIO_Label=FPGA_STATUS
PD5.Signal=GPIO_Input
PD6.GPIOParameters=GPIO_Label
PD6.GPIO_Label=FPGA_CONF_DONE
PD6.Signal=GPIO_Input
PD7.GPIOParameters=GPIO_Label
PD7.GPIO_Label=MCU_READY
PD7.Signal=GPIO_Output
PD8.GPIOParameters=GPIO_Label
PD8.GPIO_Label=FS_SEL
PD8.Signal=GPIO_Output
PD9.GPIOParameters=GPIO_Label
PD9.GPIO_Label=FPGA_PLL_LOCKED
PD9.Signal=GPIO_Input
PE0.GPIOParameters=GPIO_Label
PE0.GPIO_Label=MCU_DEBUG0
PE0.Signal=GPIO_Output
PE1.GPIOParameters=GPIO_Label
PE1.GPIO_Label=MCU_DEBUG1
PE1.Signal=GPIO_Output
PE10.GPIOParameters=GPIO_Label
PE10.GPIO_Label=ADAT_IN2_USER2
PE10.Signal=GPIO_Input
PE11.GPIOParameters=GPIO_Label
PE11.GPIO_Label=ADAT_IN2_USER3
PE11.Signal=GPIO_Input
PE12.GPIOParameters=GPIO_Label
PE12.GPIO_Label=ADAT_OUT1_USER0
PE12.Signal=GPIO_Output
PE13.GPIOParameters=GPIO_Label
PE13.GPIO_Label=ADAT_OUT1_USER1
PE13.Signal=GPIO_Output
PE14.GPIOParameters=GPIO_Label
PE14.GPIO_Label=ADAT_OUT1_USER2
PE14.Signal=GPIO_Output
PE15.GPIOParameters=GPIO_Label
PE15.GPIO_Label=ADAT_OUT1_USER3
PE15.Signal=GPIO_Output
PE2.GPIOParameters=GPIO_Label
PE2.GPIO_Label=MCU_DEBUG2
PE2.Signal=GPIO_Output
PE3.GPIOParameters=GPIO_Label
PE3.GPIO_Label=MCU_DEBUG3
PE3.Signal=GPIO_Output
PE4.GPIOParameters=GPIO_Label
PE4.GPIO_Label=ADAT_IN1_USER0
PE4.Signal=GPIO_Input
PE5.GPIOParameters=GPIO_Label
PE5.GPIO_Label=ADAT_IN1_USER1
PE5.Signal=GPIO_Input
PE6.GPIOParameters=GPIO_Label
PE6.GPIO_Label=ADAT_IN1_USER2
PE6.Signal=GPIO_Input
PE7.GPIOParameters=GPIO_Label
PE7.GPIO_Label=ADAT_IN1_USER3
PE7.Signal=GPIO_Input
PE8.GPIOParameters=GPIO_Label
PE8.GPIO_Label=ADAT_IN2_USER0
PE8.Signal=GPIO_Input
PE9.GPIOParameters=GPIO_Label
PE9.GPIO_Label=ADAT_IN2_USER1
PE9.Signal=GPIO_Input
PH0/OSC_IN.Mode=HSE-External-Oscillator
PH0/OSC_IN.Signal=RCC_OSC_IN
PH1/OSC_OUT.Mode=HSE-External-Oscillator
PH1/OSC_OUT.Signal=RCC_OSC_OUT
RCC.HSE_VALUE=24000000
RCC.SYSCLKFreq_VALUE=180000000
RCC.SYSCLKSource=RCC_SYSCLKSOURCE_PLLCLK
board=custom

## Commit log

2025-09-01 Scaffold Quartus HDL project
2025-09-03 Implement an untested nrzi decoder with phase locking
2025-09-04 Fix NRZI decoder design
2025-09-04 Change extension from .do to .tcl
2025-09-06 Implement untested adat_decoder module
2025-09-06 Fix adat_decoder to synthesize
2025-09-07 Write testbench and fix adat_decoder module
2025-09-08 Implement better nrzi decoder based on circular buffer
2025-09-08 Add user input bits
2025-09-09 Implement untested I2S MSB-justified transmitter
2025-09-09 Write testbench and fix i2s_msb_transmitter
2025-09-10 Implement I2S receiver, write I2S loopback test
2025-09-17 Implement adat_rx_channel compound module
2025-09-18 Write a test for adat_rx_channel
2025-09-21 Start implementing ADAT transmitter
2025-09-22 Move to dual clock domain design
2025-09-22 Implement untested ADAT transmitter module
2025-09-25 Implement and test full ADAT <=> I2S loopback
2025-09-25 Implement top-level FPGA module
2025-09-28 Further schematic capture
2025-09-30 Assign most of the footprints to schematic components
2025-10-01 Finish assigning footprints to project
2025-10-03 Finish drawing IO/Supply board
2025-10-04 Draw first version of display board
2025-10-04 Small display board layout improvements
2025-10-09 Add missing CAD models of I/O electronic components
2025-10-10 Start routing main board
2025-10-12 Finish first revision of main pcb
2025-10-12 Add buffers for ADAT transfer
2025-10-12 Assign FPGA pins, change MCU to STM32F429VET6
2025-10-23 Add PCB production files
2025-10-23 Provide final rev 1.0a production files
2025-11-04 Design bottom plate in cad
2025-11-04 Switch assembly workbench to A2plus
2025-11-04 Add PCB standoffs to CAD assembly
2025-11-04 Design front and top plate in CAD
2025-11-06 Close enclosure by adding back plate in CAD
2025-11-23 Add pin assignment to cubemx project
2025-11-25 Add unfinished front acrylic design
